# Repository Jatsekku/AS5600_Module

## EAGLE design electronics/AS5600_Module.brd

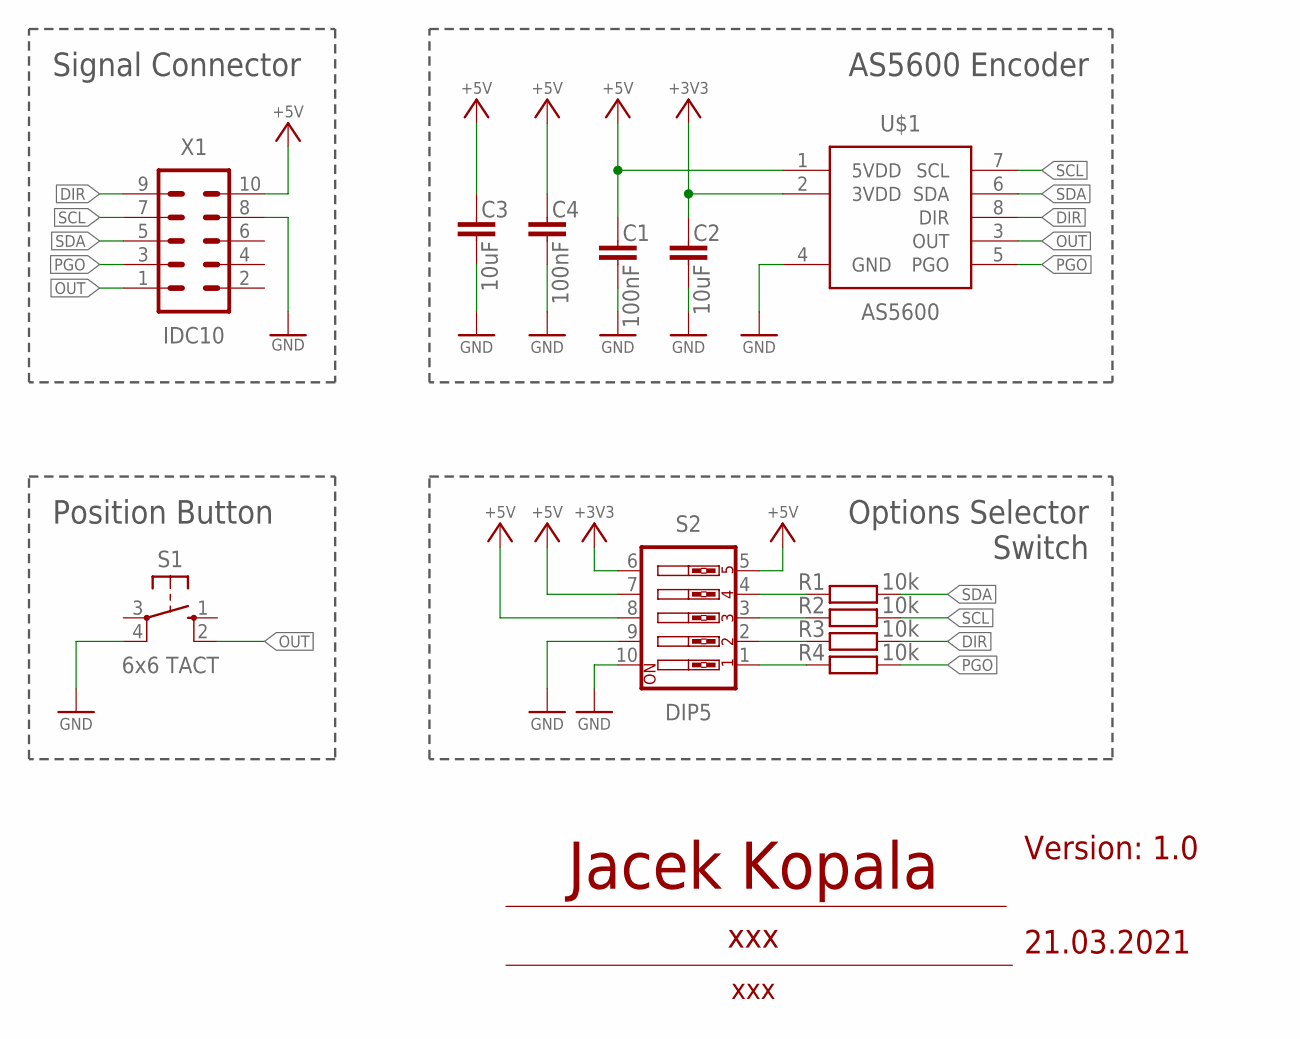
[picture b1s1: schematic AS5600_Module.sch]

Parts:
C1, C4: 100nF; C0805K
C2, C3: 10uF; C0805K
R1, R2, R3, R4: 10k; R0805
S1: 6x6 TACT; B3F-10XX
S2: DIP5; EDG-05
U$1: AS5600; SO8
X1: IDC10; ML10

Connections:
+3V3: C2.1, S2.6, U$1.2 (3VDD)
+5V: C1.1, C3.1, C4.1, S2.5, S2.7, S2.8, U$1.1 (5VDD), X1.10
DIR: R3.1, U$1.8 (DIR), X1.9
GND: C1.2, C2.2, C3.2, C4.2, S1.4 (P1), S2.9, S2.10, U$1.4 (GND), X1.8
unnamed: R3.2, S2.2
unnamed: R2.2, S2.3
unnamed: R1.2, S2.4
unnamed: R4.2, S2.1
OUT: S1.2 (S1), U$1.3 (OUT), X1.1
PGO: R4.1, U$1.5 (PGO), X1.3
SCL: R2.1, U$1.7 (SCL), X1.7
SDA: R1.1, U$1.6 (SDA), X1.5

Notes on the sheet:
Signal Connector
AS5600 Encoder
Position Button
Options Selector Switch
Version: 1.0
21.03.2021
Jacek Kopala
xxx

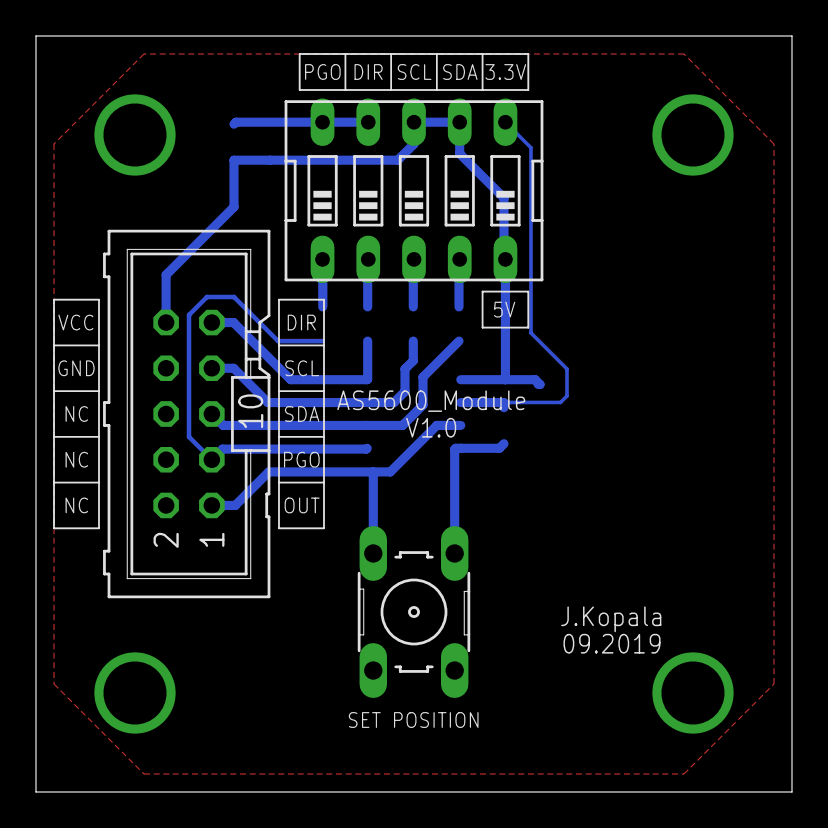
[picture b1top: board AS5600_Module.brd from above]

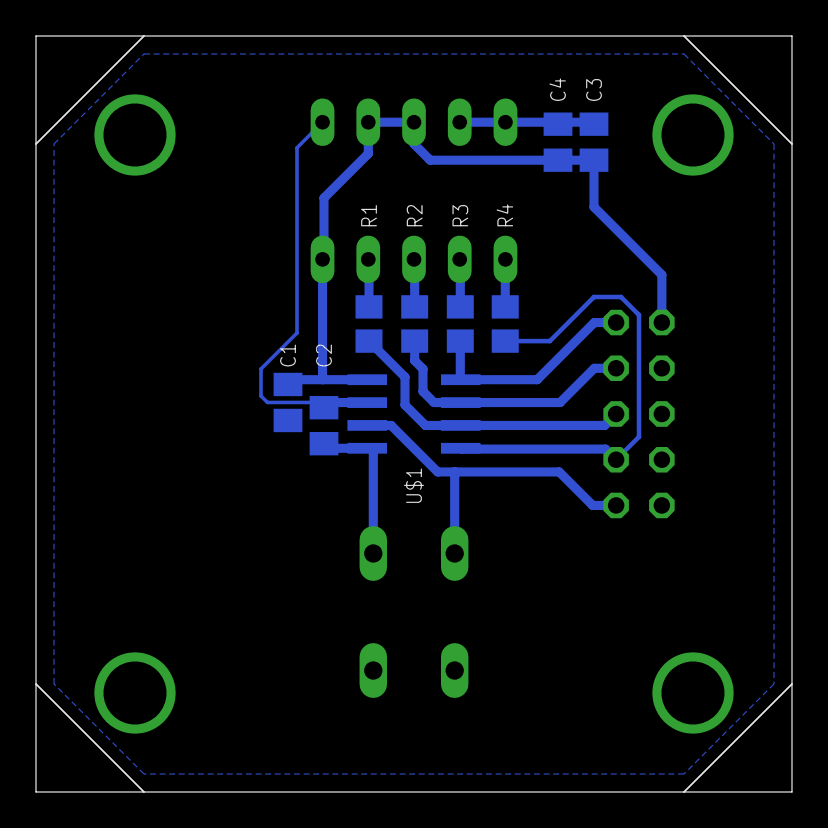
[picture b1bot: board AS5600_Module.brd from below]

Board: 2 copper layers, 42.0 x 42.0 mm, 12 parts (9 on the bottom side), 12 nets.

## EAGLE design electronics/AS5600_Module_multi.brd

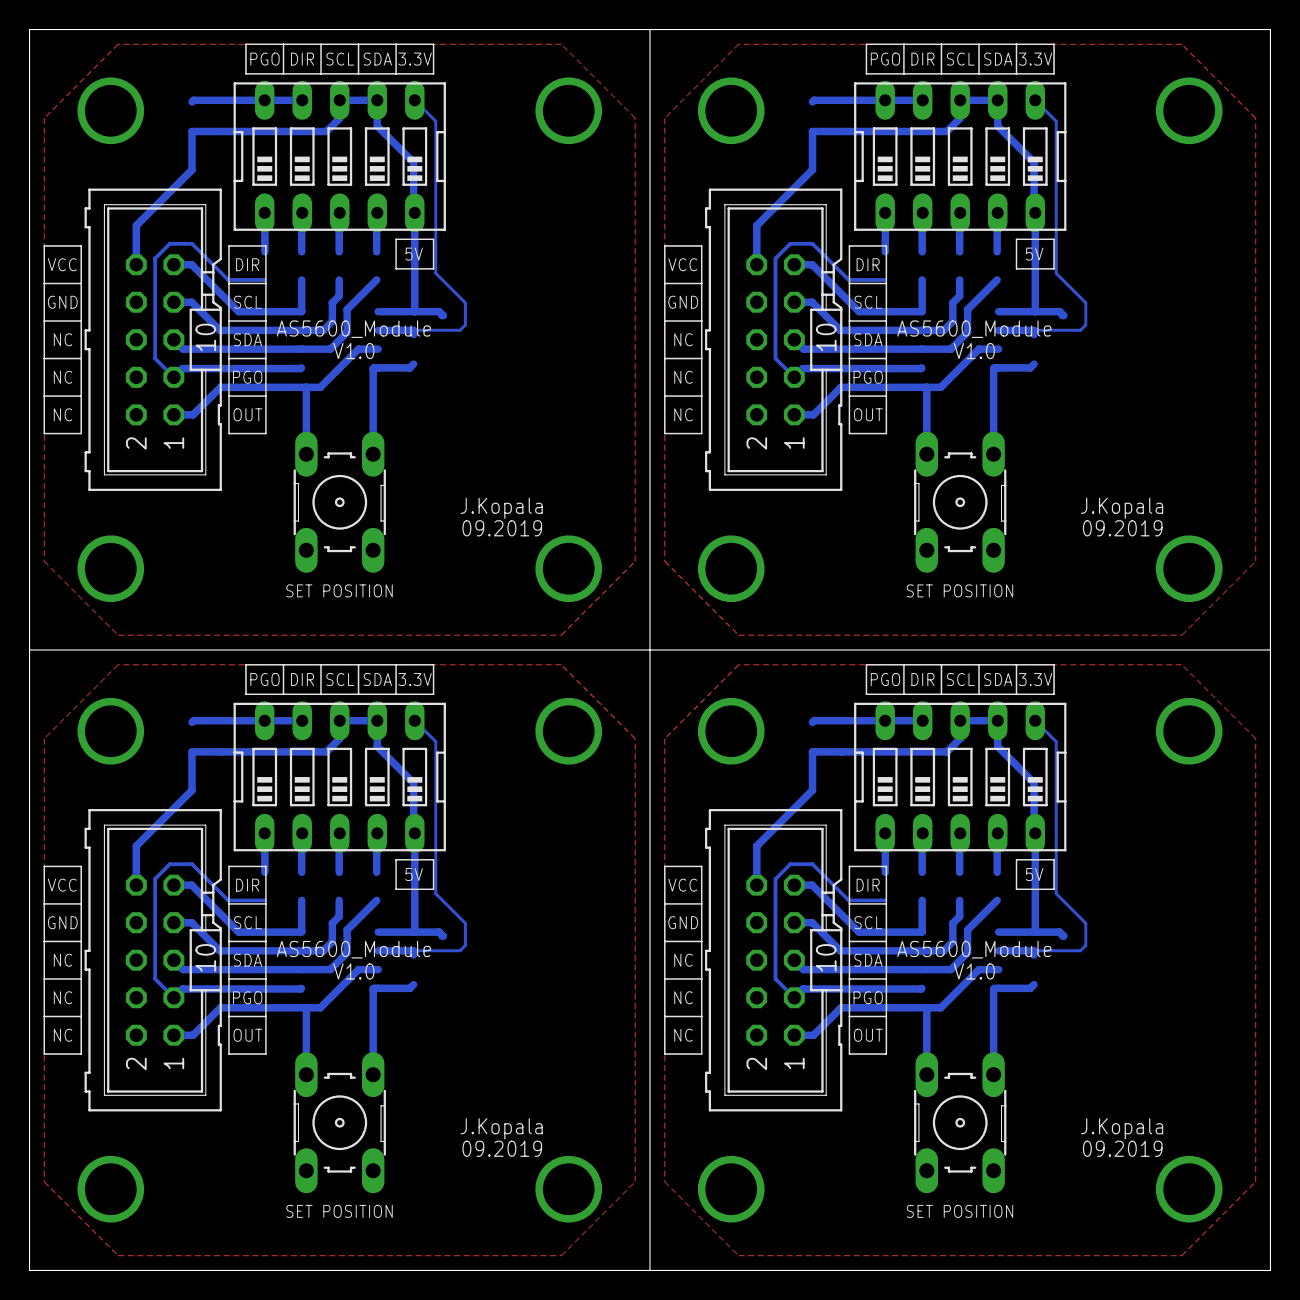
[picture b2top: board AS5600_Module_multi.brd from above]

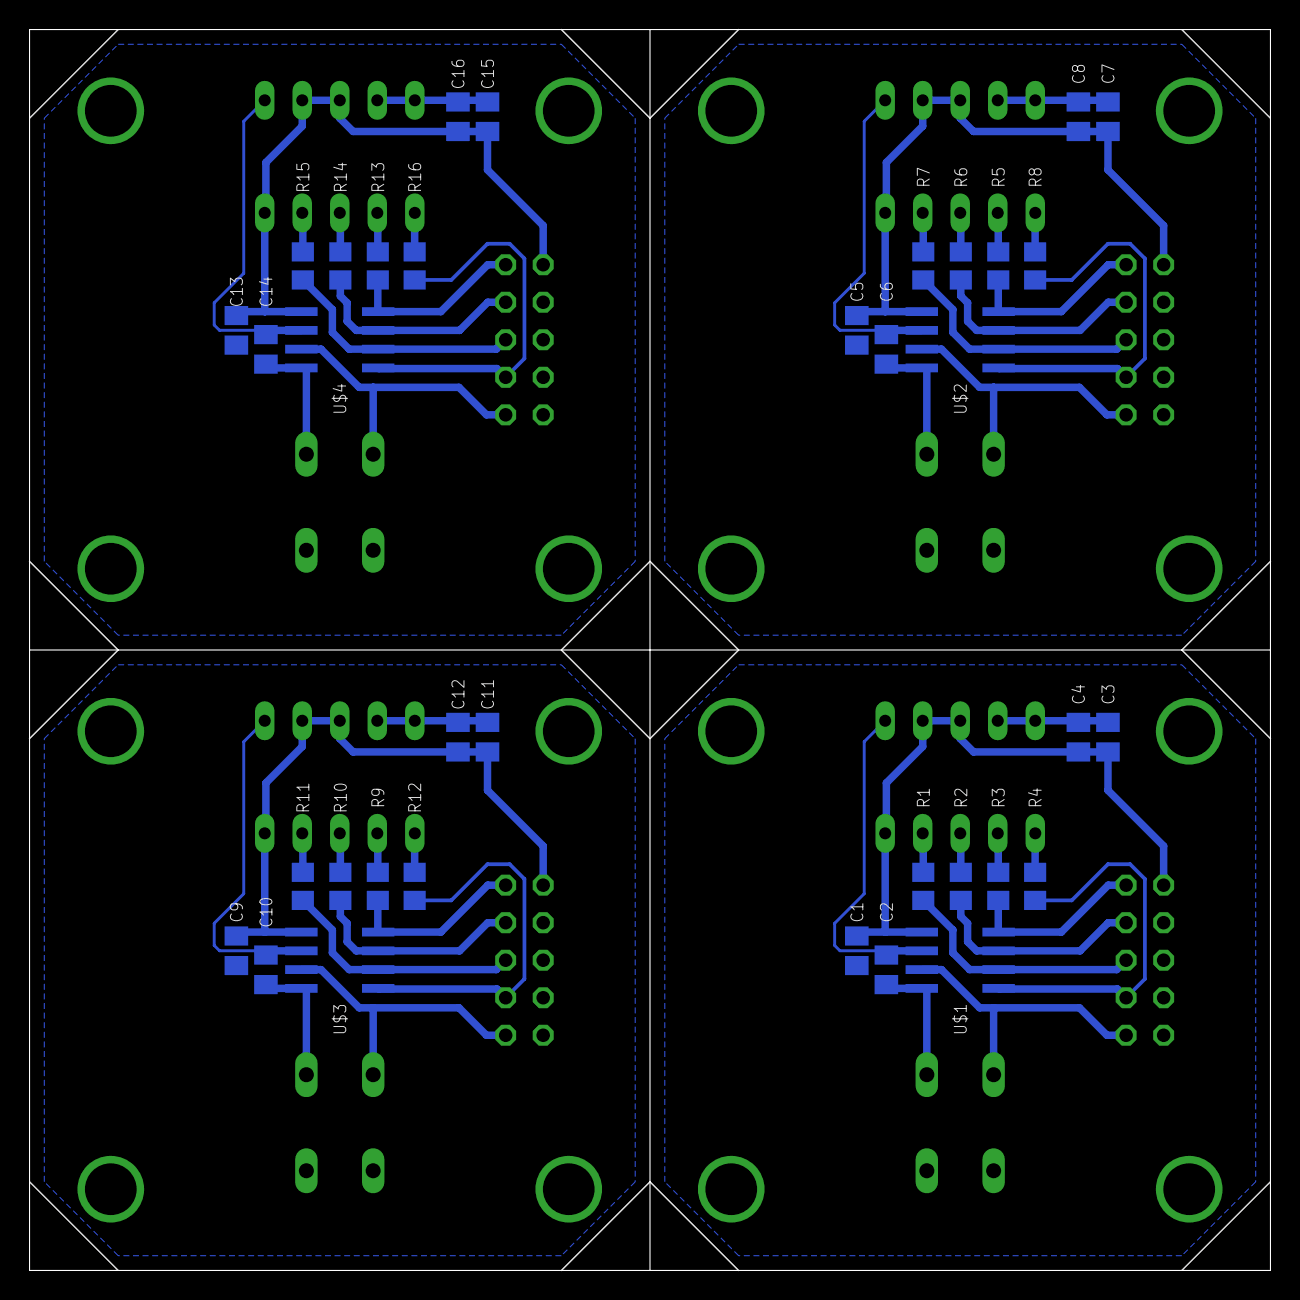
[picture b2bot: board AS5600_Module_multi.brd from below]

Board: 2 copper layers, 84.0 x 84.0 mm, 48 parts (36 on the bottom side), 48 nets.

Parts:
C1, C4, C5, C8, C9, C12, C13, C16: 100nF; C0805K
C2, C3, C6, C7, C10, C11, C14, C15: 10uF; C0805K
CON1, CON2, CON3, CON4: ML10
R1, R2, R3, R4, R5, R6, R7, R8, R9, R10, R11, R12, R13, R14, R15, R16: R0805
S1, S4, S6, S8: B3F-10XX
S2, S3, S5, S7: EDG-05
U$1, U$2, U$3, U$4: AS5600; SO8

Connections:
+3V1: C6.1, S3.6, U$2.2
+3V2: C10.1, S5.6, U$3.2
+3V3: C2.1, S2.6, U$1.2
+3V4: C14.1, S7.6, U$4.2
+5V: C1.1, C3.1, C4.1, CON1.10, S2.5, S2.7, S2.8, U$1.1
+5V1: C5.1, C7.1, C8.1, CON2.10, S3.5, S3.7, S3.8, U$2.1
+5V2: C9.1, C11.1, C12.1, CON3.10, S5.5, S5.7, S5.8, U$3.1
+5V3: C13.1, C15.1, C16.1, CON4.10, S7.5, S7.7, S7.8, U$4.1
DIR: CON1.9, R3.1, U$1.8
DIR1: CON2.9, R5.1, U$2.8
DIR2: CON3.9, R9.1, U$3.8
DIR3: CON4.9, R13.1, U$4.8
GND: C1.2, C2.2, C3.2, C4.2, CON1.8, S1.4, S2.9, S2.10, U$1.4
GND1: C5.2, C6.2, C7.2, C8.2, CON2.8, S3.9, S3.10, S4.4, U$2.4
GND2: C9.2, C10.2, C11.2, C12.2, CON3.8, S5.9, S5.10, S6.4, U$3.4
GND3: C13.2, C14.2, C15.2, C16.2, CON4.8, S7.9, S7.10, S8.4, U$4.4
unnamed: R5.2, S3.2
unnamed: R6.2, S3.3
unnamed: R3.2, S2.2
unnamed: R2.2, S2.3
unnamed: R1.2, S2.4
unnamed: R4.2, S2.1
unnamed: R7.2, S3.4
unnamed: R8.2, S3.1
unnamed: R9.2, S5.2
unnamed: R10.2, S5.3
unnamed: R11.2, S5.4
unnamed: R12.2, S5.1
unnamed: R13.2, S7.2
unnamed: R14.2, S7.3
unnamed: R15.2, S7.4
unnamed: R16.2, S7.1
OUT: CON1.1, S1.2, U$1.3
OUT1: CON2.1, S4.2, U$2.3
OUT2: CON3.1, S6.2, U$3.3
OUT3: CON4.1, S8.2, U$4.3
PGO: CON1.3, R4.1, U$1.5
PGO1: CON2.3, R8.1, U$2.5
PGO2: CON3.3, R12.1, U$3.5
PGO3: CON4.3, R16.1, U$4.5
SCL: CON1.7, R2.1, U$1.7
SCL1: CON2.7, R6.1, U$2.7
SCL2: CON3.7, R10.1, U$3.7
SCL3: CON4.7, R14.1, U$4.7
SDA: CON1.5, R1.1, U$1.6
SDA1: CON2.5, R7.1, U$2.6
SDA2: CON3.5, R11.1, U$3.6
SDA3: CON4.5, R15.1, U$4.6
